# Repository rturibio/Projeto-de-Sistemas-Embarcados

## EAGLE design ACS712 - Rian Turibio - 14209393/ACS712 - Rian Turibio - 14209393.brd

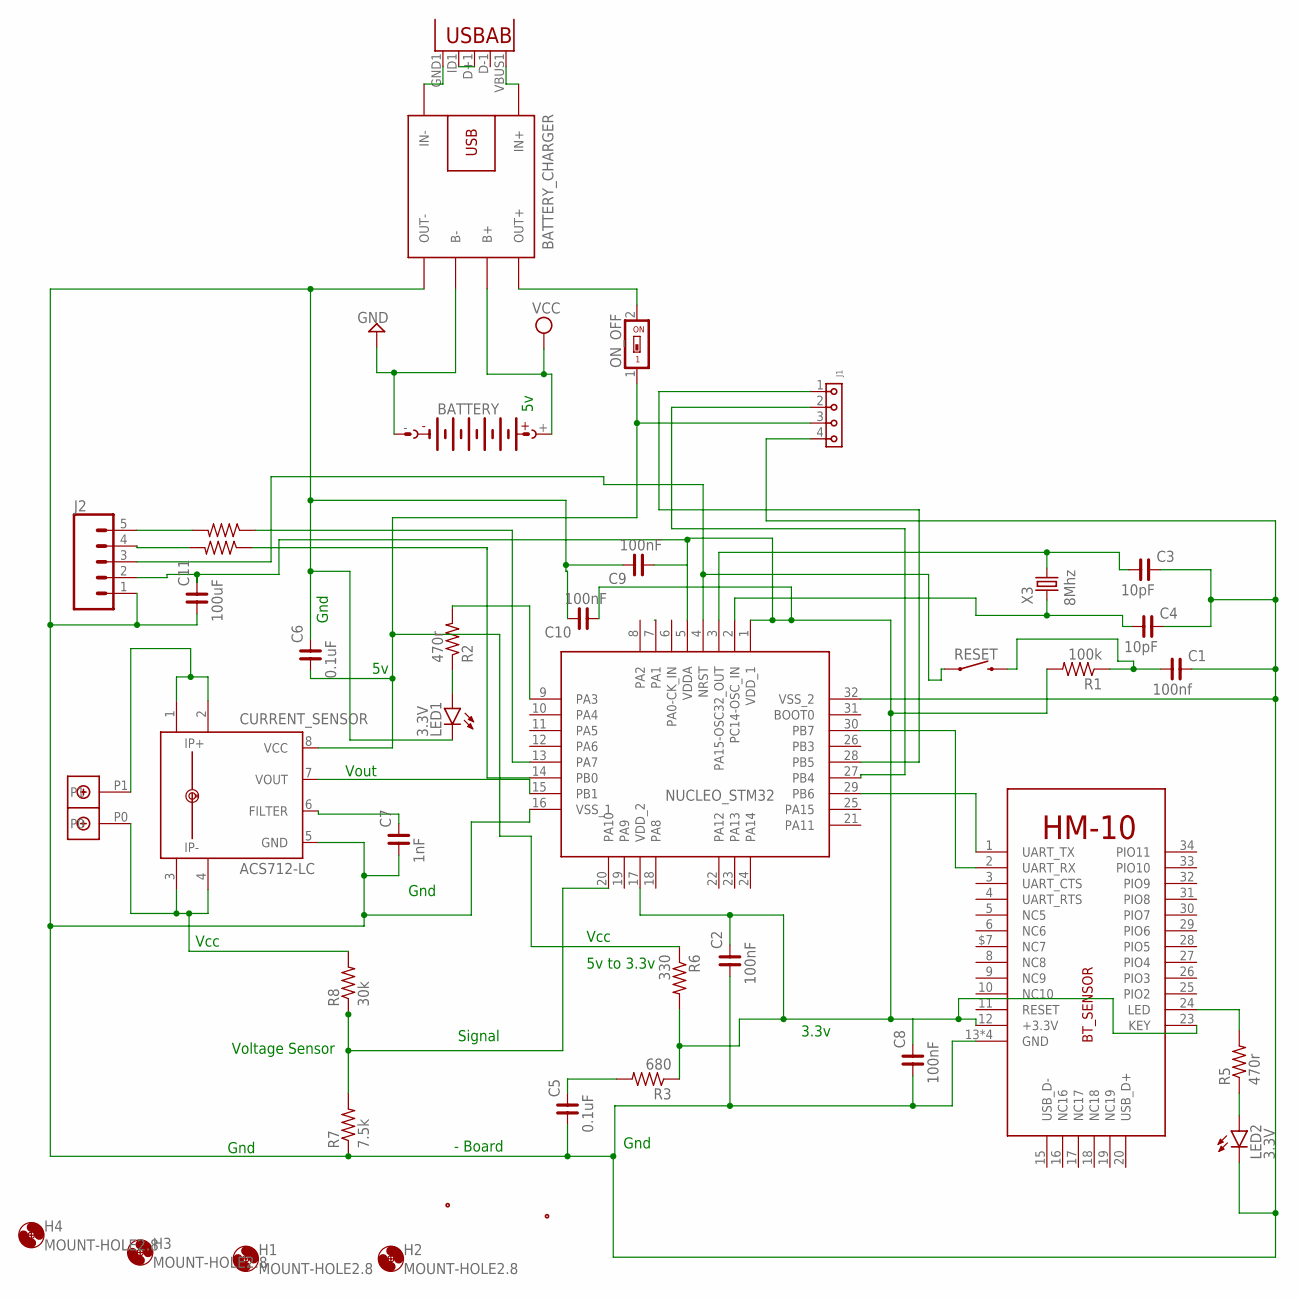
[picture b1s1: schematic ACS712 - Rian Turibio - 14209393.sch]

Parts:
BATTERY: AB9V
BATTERY_CHARGER: BATTERY-CHARGER-LI-PROT
BT_SENSOR: HM-10-BOARD; 26.9X13X2.2_BOARD
C1: 100nf; C0805
C2, C8, C9, C10: 100nF; C0805
C3, C4: 10pF; C0805
C5, C6: 0.1uF; C0805
C7: 1nF; C0805
C11: 100uF; C0805
CURRENT_SENSOR: ACS712-LC; SOIC8
H1, H2, H3, H4: MOUNT-HOLE2.8; 2,8
J1: 6130XX11821_61300411821; 61300411821
J2: CONN_05; 1X05
LED1, LED2: 3.3V; CHIPLED_0805
NUCLEO_STM32: STM32L031K6T6TR; QFP80P900X900X160-32N
ON_OFF: SWS001; SMS-001
R1: 100k; RES_0805
R2, R5: 470r; RES_0805
R3: 680; RES_0805
R4, R9: 10k; RES_0805
R6: 330; RES_0805
R7: 7.5k; RES_0805
R8: 30k; RES_0805
RESET: MOMENTARY-SWITCH-SPST-SMD-6.0X3.5MM; TACTILE_SWITCH_SMD_6.0X3.5MM
U1: 5v; USB-MICRO-SMD
U$2: DBCONN-1X2
X1, X2: FIDUCIAL_0.6-1.2MM; FIDUCIAL0.6-1.2
X3: 8Mhz; 5032/2P

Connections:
GND: BATTERY.-, BATTERY_CHARGER.B-
unnamed: BATTERY_CHARGER.OUT+, ON_OFF.2
unnamed: NUCLEO_STM32.20 (PA10), R7.2, R8.1
unnamed: BT_SENSOR.24 (LED), R5.2
unnamed: U1.D+1 (D+), U1.ID1 (USBID)
unnamed: CURRENT_SENSOR.7 (VOUT), NUCLEO_STM32.15 (PB1)
unnamed: BT_SENSOR.1 (UART_TX), NUCLEO_STM32.29 (PB6)
unnamed: C7.2, CURRENT_SENSOR.6 (FILTER)
unnamed: J1.1, NUCLEO_STM32.28 (PB5)
unnamed: CURRENT_SENSOR.1 (IP+), CURRENT_SENSOR.2 (IP+1), U$2.P1
unnamed: J1.2, NUCLEO_STM32.27 (PB4)
unnamed: BT_SENSOR.12 (+3.3V), BT_SENSOR.23 (KEY), C2.2, C8.2, C9.1, C10.1, C11.2, J2.2, NUCLEO_STM32.1 (VDD_1), NUCLEO_STM32.5 (VDDA), NUCLEO_STM32.17 (VDD_2), R1.2, R3.1, R6.2
unnamed: CURRENT_SENSOR.3 (IP-), CURRENT_SENSOR.4 (IP-1), R8.2, U$2.P0
unnamed: C6.1, CURRENT_SENSOR.8 (VCC), J1.3, ON_OFF.1, R6.1
unnamed: J2.3, NUCLEO_STM32.4 (NRST), RESET.1
unnamed: LED2.A, R5.1
unnamed: BATTERY_CHARGER.IN-, U1.GND1 (GND)
unnamed: BATTERY_CHARGER.IN+, U1.VBUS1 (VBUS)
unnamed: C4.1, NUCLEO_STM32.2 (PC14-OSC_IN), X3.1
unnamed: BT_SENSOR.2 (UART_RX), NUCLEO_STM32.30 (PB7)
unnamed: C3.1, NUCLEO_STM32.3 (PA15-OSC32_OUT), X3.2
unnamed: BATTERY_CHARGER.OUT-, BT_SENSOR.13 (GND), BT_SENSOR.14 (GND), BT_SENSOR.21 (GND), BT_SENSOR.22 (GND), C1.2, C2.1, C3.2, C4.2, C5.1, C6.2, C7.1, C8.1, C9.2, C10.2, C11.1, CURRENT_SENSOR.5 (GND), J1.4, J2.1, LED1.C, LED2.C, NUCLEO_STM32.16 (VSS_1), NUCLEO_STM32.32 (VSS_2), R7.1
unnamed: NUCLEO_STM32.9 (PA3), R2.2
unnamed: C5.2, R3.2
unnamed: C1.1, R1.1, RESET.2
unnamed: LED1.A, R2.1
unnamed: NUCLEO_STM32.13 (PA7), R4.1
unnamed: NUCLEO_STM32.14 (PB0), R9.1
unnamed: J2.5, R4.2
unnamed: J2.4, R9.2
VCC: BATTERY.+, BATTERY_CHARGER.B+

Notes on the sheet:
Vcc
Gnd
Signal
- Board
Voltage Sensor
Vout
3.3v
5v to 3.3v

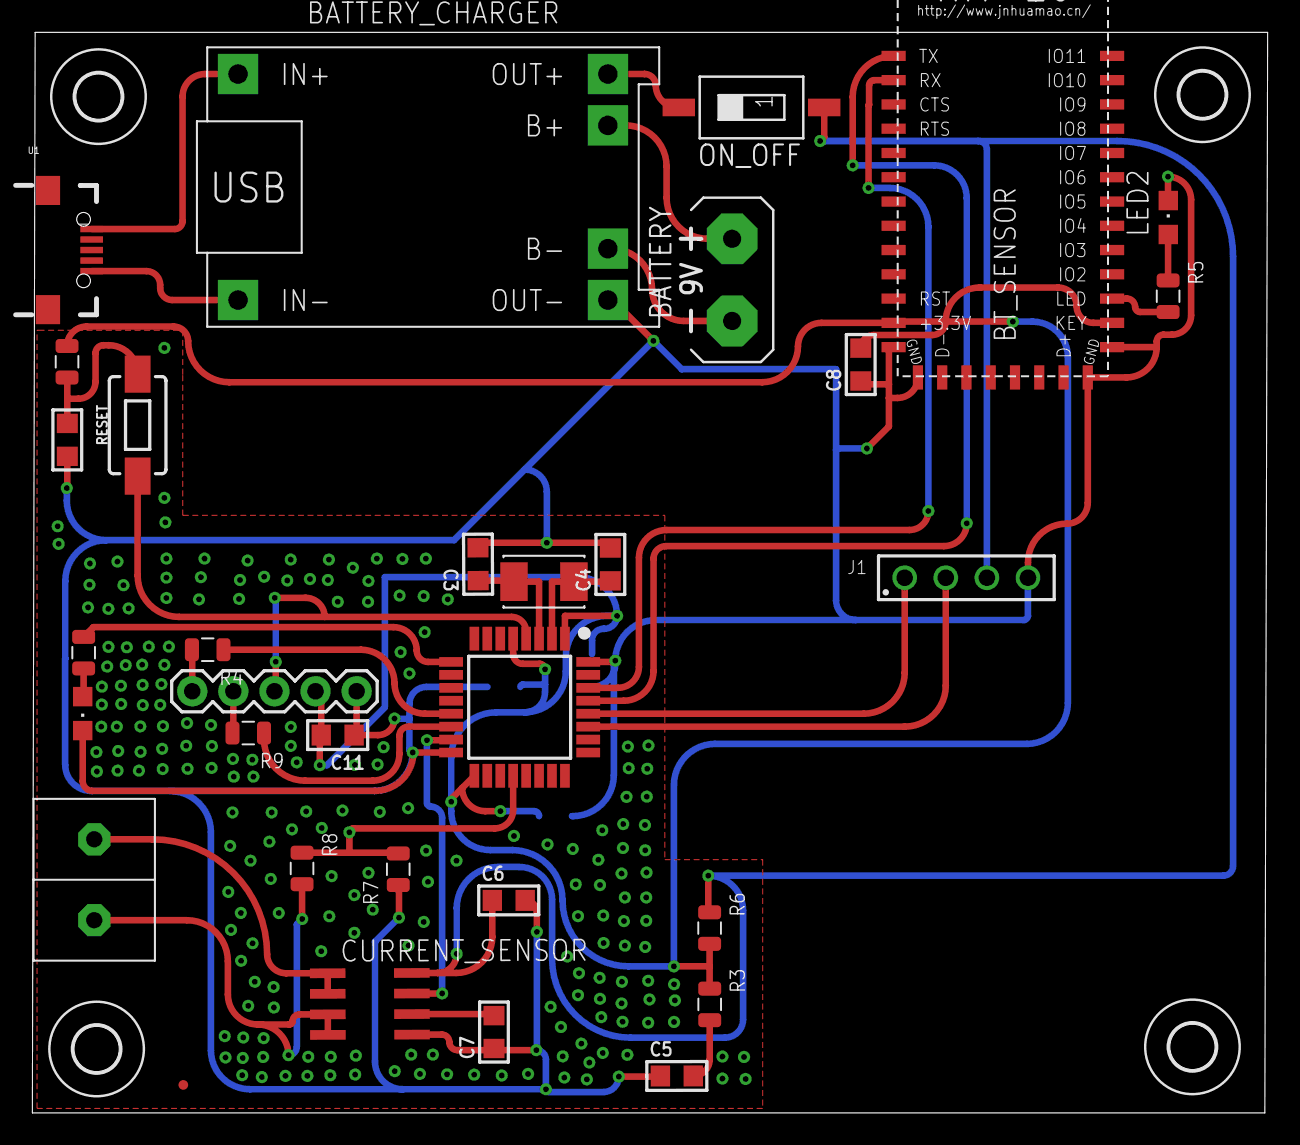
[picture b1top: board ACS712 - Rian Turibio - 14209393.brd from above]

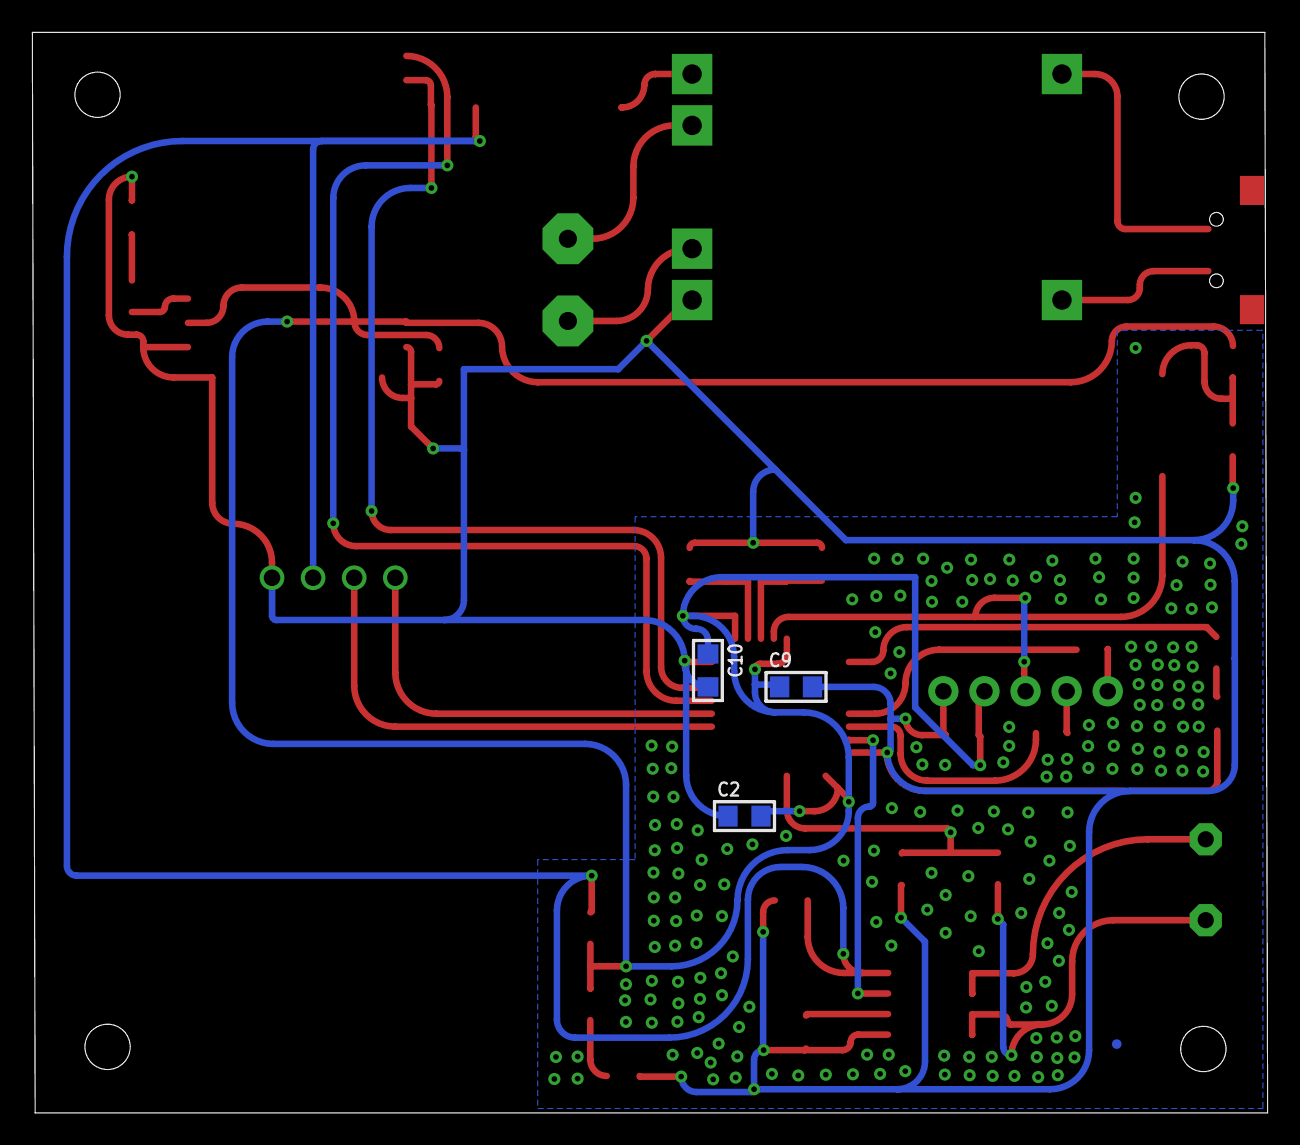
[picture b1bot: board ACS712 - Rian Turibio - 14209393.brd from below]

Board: 2 copper layers, 76.4 x 66.8 mm, 40 parts (4 on the bottom side), 31 nets.

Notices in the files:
parts and their libraries:
diy-modules: Released under the Creative Commons Attribution 4.0 International License: http://creativecommons.org/licenses/by/4.0
rc-master-smd: Copyright (C) 2007, Bob Starr
Wurth_Connectors_WR-PHD: Copyright: Würth Elektronik
